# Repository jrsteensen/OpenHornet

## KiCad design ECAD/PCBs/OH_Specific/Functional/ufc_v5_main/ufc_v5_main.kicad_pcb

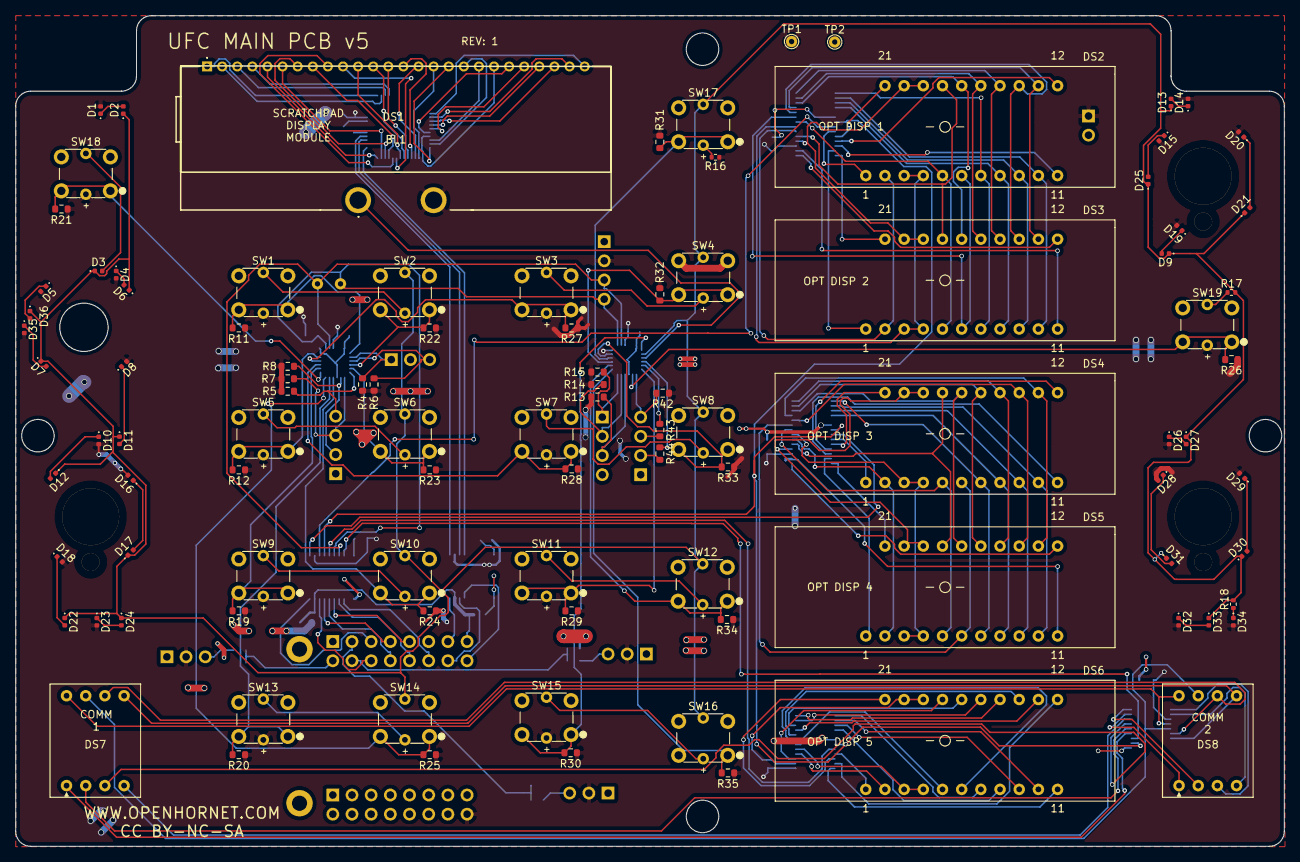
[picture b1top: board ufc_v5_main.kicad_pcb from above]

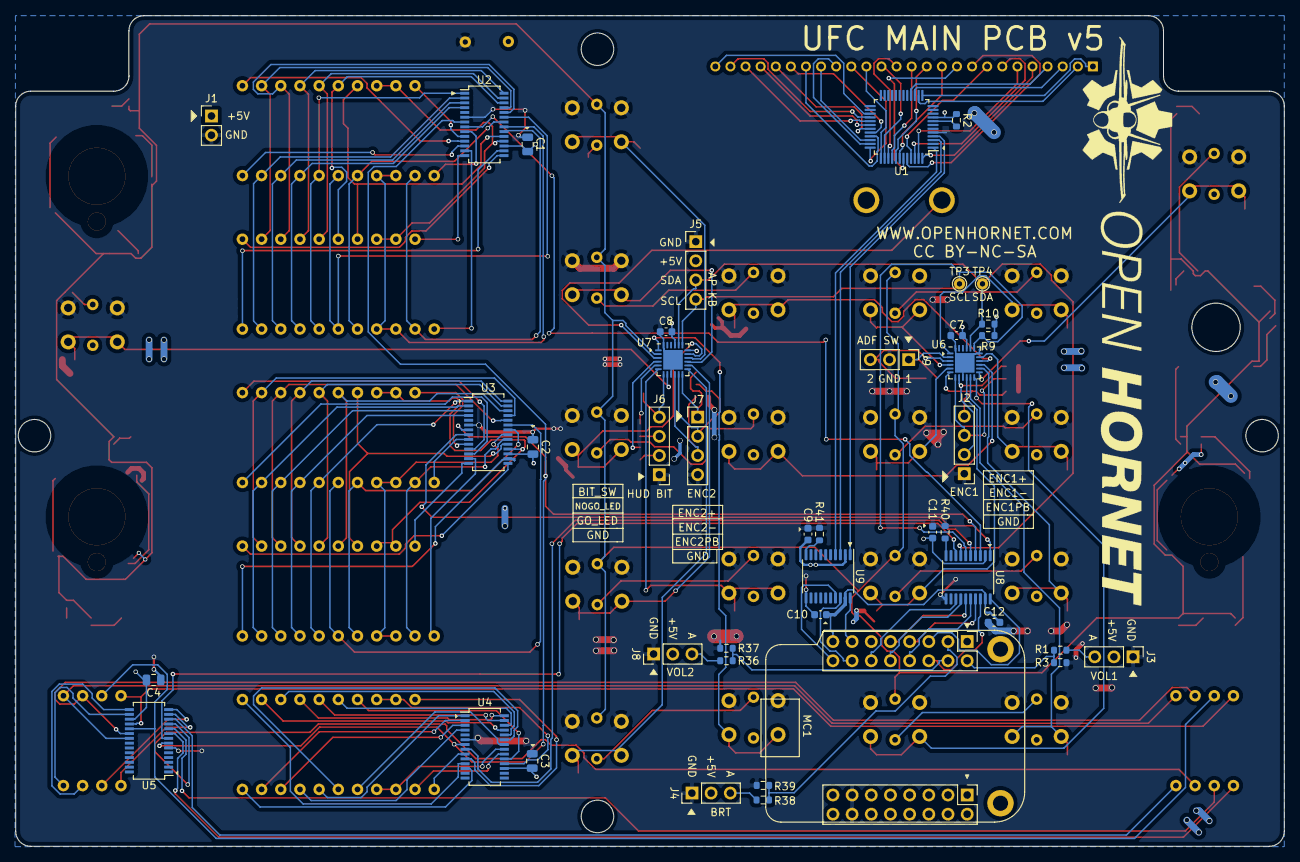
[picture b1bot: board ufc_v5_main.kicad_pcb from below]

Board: 2 copper layers, 168.0 x 110.0 mm, 149 parts (42 on the bottom side), 198 nets.

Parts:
BL1: UFCScratchPadBacklight; SCRATCHPADBACKLIGHT
C1, C2, C3, C4: 10uF; C_0805_2012Metric
C7, C8, C9, C10, C11, C12: .1uF; C_0603_1608Metric
D1, D2, D3, D4, D5, D6, D7, D8, D9, D10, D11, D12, D13, D14, D15, D16, D17, D18, D19, D20, D21, D22, D23, D24, D25, D26, D27, D28, D29, D30, D31, D32, D33, D34, D35, D36: LED_0402_1005Metric
DS1: UFCScratchpadLCD; SCRATCHPADLCD
DS2, DS3, DS4, DS5, DS6: UFCOptionDigit
DS7, DS8: UFCSingleDigit
J1: +5VIN; PinHeader_1x02_P2.54mm_Vertical
J2: ENC1; PinHeader_1x04_P2.54mm_Vertical
J3: VOL1; PinHeader_1x03_P2.54mm_Vertical
J4: BRT; PinHeader_1x03_P2.54mm_Vertical
J5: AP KB; PinHeader_1x04_P2.54mm_Vertical
J6: HUD BIT; PinHeader_1x04_P2.54mm_Vertical
J7: ENC2; PinHeader_1x04_P2.54mm_Vertical
J8: VOL2; PinHeader_1x03_P2.54mm_Vertical
J9: ADF SW; PinHeader_1x03_P2.54mm_Vertical
MC1: S2_MINI
MK1, MK2, MK3, MK4: MH; MountingHole_4.3mm_M4
MK5: SW_ADF; MountingHole_6.4mm_M6
POT1: VOL1; BR10K_Pot_11mm_x_11mm
POT2: VOL2; BR10K_Pot_11mm_x_11mm
POT3: BRT; BR10K_Pot_11mm_x_11mm
R1, R36, R38: 1k; R_0603_1608Metric
R2: 10K; R_0603_1608Metric
R3, R37, R39: 2K; R_0603_1608Metric
R4, R5, R6, R7, R8, R9, R10, R11, R12, R13, R14, R15, R19, R20, R21, R22, R23, R24, R25, R26, R27, R28, R29, R30, R31, R32, R33, R34, R35, R40, R41, R42: 4.7k; R_0603_1608Metric
R16, R17, R18: 33; R_0402_1005Metric
R43, R44: 68; R_0603_1608Metric
SW1, SW2, SW3, SW4, SW5, SW6, SW7, SW8, SW9, SW10, SW11, SW12, SW13, SW14, SW15, SW16, SW17, SW18, SW19: TL1240GQ
TP1: 5V; TestPoint_THTPad_D1.5mm_Drill0.7mm
TP2: GND; TestPoint_THTPad_D1.5mm_Drill0.7mm
TP3: SCL; TestPoint_THTPad_D1.5mm_Drill0.7mm
TP4: SDA; TestPoint_THTPad_D1.5mm_Drill0.7mm
U1: HT1621B; LQFP-48_7x7mm_P0.5mm
U2, U3, U4, U5: GN1640T; SSOP-28_3.9x9.9mm_P0.635mm
U6, U7: AW9523BTQR; WQFN-24-1EP_4x4mm_P0.5mm_EP2.6x2.6mm
U8, U9: TXS0108EPW; TSSOP-20_4.4x6.5mm_P0.65mm

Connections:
+3V3: C10.2, C12.2, MC1.8, U8.19, U9.19
+5V: BL1.2, C1.2, C2.2, C3.2, C4.2, C7.2, C8.2, C9.2, C11.2, D1.2, D4.2, D5.2, D8.2, D10.2, D14.2, D15.2, D16.2, D18.2, D19.2, D20.2, D23.2, D26.2, D28.2, D29.2, D32.2, D34.2, D35.2, J1.1, J3.2, J4.2, J5.2, J8.2, MC1.32, R2.1, R4.1, R5.2, R6.2, R7.2, R8.1, R9.1, R10.2, R11.1, R12.1, R13.1, R14.2, R15.1, R16.1, R19.1, R20.1, R21.1, R22.1, R23.1, R24.1, R25.1, R26.1, R27.1, R28.1, R29.1, R30.1, R31.1, R32.1, R33.1, R34.1, R35.1, R42.1, SW1.5, SW3.5, SW5.5, SW7.5, SW9.5, SW11.5, SW13.5, SW15.5, SW18.5, SW19.5, TP1.1, U1.9, U2.17, U3.17, U4.17, U5.17, U6.21, U7.18, U7.21, U8.2, U9.2
/0+: SW13.6, SW14.5
/0-: D2.1, D3.1, D6.1, D7.1, D9.1, D11.1, D12.1, D13.1, D17.1, D21.1, D22.1, D24.1, D25.1, D27.1, D30.1, D31.1, D33.1, D36.1, R17.2, R18.2, SW2.6, SW4.6, SW6.6, SW8.6, SW10.6, SW12.6, SW14.6, SW16.6, SW17.6, U7.2
/1-: SW1.6, SW2.5
/1AB: DS2.19, DS2.20, DS3.19, DS3.20, U2.18
/1C: DS2.18, DS3.18, U2.19
/1D: DS2.2, DS3.2, U2.20
/1DP: DS2.8, DS3.8, U2.4
/1EF: DS2.3, DS2.4, DS3.3, DS3.4, U2.21
/1G: DS2.5, DS3.5, U2.22
/1H: DS2.6, DS3.6, U2.23
/1I: DS2.13, DS3.13, U2.25
/1J: DS2.14, DS3.14, U2.24
/1K: DS2.15, DS3.15, U2.28
/1L: DS2.16, DS3.16, U2.27
/1M: DS2.17, DS3.17, U2.26
/1N: DS2.9, DS3.9, U2.3
/1O: DS2.10, DS3.10, U2.2
/1P: DS2.7, DS3.7, U2.1
/2AB: DS4.19, DS4.20, DS5.19, DS5.20, U3.18
/2C: DS4.18, DS5.18, U3.19
/2D: DS4.2, DS5.2, U3.20
/2DP: DS4.8, DS5.8, U3.4
/2EF: DS4.3, DS4.4, DS5.3, DS5.4, U3.21
/2G: DS4.5, DS5.5, U3.22
/2H: DS4.6, DS5.6, U3.23
/2I: DS4.13, DS5.13, U3.25
/2J: DS4.14, DS5.14, U3.24
/2K: DS4.15, DS5.15, U3.28
/2L: DS4.16, DS5.16, U3.27
/2M: DS4.17, DS5.17, U3.26
/2N: DS4.9, DS5.9, U3.3
/2O: DS4.10, DS5.10, U3.2
/2P: DS4.7, DS5.7, U3.1
/3-: SW3.6, SW4.5
/3AB: DS6.19, DS6.20, U4.18
/3C: DS6.18, U4.19
/3D: DS6.2, U4.20
/3DP: DS6.8, U4.4
/3EF: DS6.3, DS6.4, U4.21
/3G: DS6.5, U4.22
/3H: DS6.6, U4.23
/3I: DS6.13, U4.25
/3J: DS6.14, U4.24
/3K: DS6.15, U4.28
/3L: DS6.16, U4.27
/3M: DS6.17, U4.26
/3N: DS6.9, U4.3
/3O: DS6.10, U4.2
/3P: DS6.7, U4.1
/4-: SW5.6, SW6.5
/6-: SW7.6, SW8.5
/7-: SW9.6, SW10.5
/9-: SW11.6, SW12.5
/ADF1: J9.1, R4.2, U6.2
/ADF2: J9.3, R6.1, U6.3
/BIT_SW: J6.4, R42.2, U7.7
/CLR-: SW15.6, SW16.5
/COM0: DS1.1, U1.13
/COM1: DS1.2, U1.14
/COM2: DS1.3, U1.15
/COM3: DS1.4, U1.16
/C_GRID1: DS7.8, DS8.8, U5.18
/C_GRID2: DS7.7, DS8.7, U5.19
/C_GRID3: DS7.6, DS8.6, U5.20
/C_GRID4: DS7.5, DS8.5, U5.21
/C_SEG1: DS7.1, U5.9
/C_SEG2: DS7.2, U5.10
/C_SEG3: DS7.3, U5.11
/C_SEG4: DS7.4, U5.12
/C_SEG5: DS8.1, U5.13
/C_SEG6: DS8.2, U5.14
/C_SEG7: DS8.3, U5.15
/C_SEG8: DS8.4, U5.16
/EM-: R17.1, SW19.6
/ENC1+: J2.4, R5.1, U6.6
/ENC1-: J2.3, R7.1, U6.7
/ENC1PB: J2.2, R8.2, U6.8
/ENC2+: J7.1, R15.2, U7.12
/ENC2-: J7.2, R14.1, U7.11
/ENC2PB: J7.3, R13.2, U7.10
/GO_LED: J6.2, R44.2
/IP-: D3.2, SW18.6
/NOGO_LED: J6.3, R43.2
/OP1+: R16.2, SW17.5
/OP1D1: DS2.1, U2.9
/OP1D2: DS2.21, U2.10
/OP1D3: DS2.12, U2.11
/OP1D4: DS2.11, U2.12
/OP2D1: DS3.1, U2.13
/OP2D2: DS3.21, U2.14
/OP2D3: DS3.12, U2.15
/OP2D4: DS3.11, U2.16
/OP3D1: DS4.1, U3.9
/OP3D2: DS4.21, U3.10
/OP3D3: DS4.12, U3.11
/OP3D4: DS4.11, U3.12
/OP4D1: DS5.1, U3.13
/OP4D2: DS5.21, U3.14
/OP4D3: DS5.12, U3.15
/OP4D4: DS5.11, U3.16
/OP5D1: DS6.1, U4.9
/OP5D2: DS6.21, U4.10
/OP5D3: DS6.12, U4.11
/OP5D4: DS6.11, U4.12
/SEG0: DS1.5, U1.48
/SEG1: DS1.6, U1.47
/SEG2: DS1.7, U1.46
/SEG3: DS1.8, U1.45
/SEG4: DS1.9, U1.44
/SEG5: DS1.10, U1.43
/SEG6: DS1.11, U1.42
/SEG7: DS1.12, U1.41
/SEG8: DS1.13, U1.40
/SEG9: DS1.14, U1.39
/SEG10: DS1.15, U1.38
/SEG11: DS1.16, U1.37
/SEG12: DS1.17, U1.36
/SEG13: DS1.18, U1.35
/SEG14: DS1.19, U1.34
/SEG15: DS1.20, U1.33
/SEG16: DS1.21, U1.32
/SEG17: DS1.22, U1.31
/SEG18: DS1.23, U1.30
/SEG19: DS1.24, U1.29
/SEG20: DS1.25, U1.28
/SEG21: DS1.26, U1.27
/SW1: R11.2, SW1.1, U6.1
/SW2: R22.2, SW2.1, U6.4
/SW3: R27.2, SW3.1, U6.16
/SW4: R12.2, SW5.1, U6.17
/SW5: R23.2, SW6.1, U6.5
/SW6: R28.2, SW7.1, U6.15
/SW7: R19.2, SW9.1, U6.14
/SW8: R24.2, SW10.1, U6.10
/SW9: R29.2, SW11.1, U7.6
/SW10: R30.2, SW15.1, U7.1
/SW11: R20.2, SW13.1, U6.11
/SW12: R25.2, SW14.1, U6.12
/SW13: R21.2, SW18.1, U6.13
/SW14: R31.2, SW17.1, U7.16
/SW15: R32.2, SW4.1, U7.15
/SW16: R33.2, SW8.1, U7.17
/SW17: R34.2, SW12.1, U7.14
/SW18: R35.2, SW16.1, U7.13
/SW19: R26.2, SW19.1, U7.8
/TNLEDPWR: BL1.1, U7.3
ANALOG1: J3.3, R1.1
ANALOG1@3.3V: MC1.9, R1.2, R3.1
ANALOG2: J8.3, R36.1
ANALOG2@3.3V: MC1.10, R36.2, R37.1
ANALOG3: J4.3, R38.1
ANALOG3@3.3V: MC1.2, R38.2, R39.1
C_CLK: U5.8, U8.8
C_CLK@3.3V: MC1.14, U8.13
DIO: U2.7, U3.7, U4.7, U5.7, U8.4
DIO@3.3V: MC1.4, U8.17
GND: C1.1, C2.1, C3.1, C4.1, C7.1, C8.1, C9.1, C10.1, C11.1, C12.1, J1.2, J2.1, J3.1, J4.1, J5.1, J6.1, J7.4, J8.1, J9.2, MC1.23, MC1.31, R3.2, R37.2, R39.2, R40.2, R41.2, SW1.2, SW2.2, SW3.2, SW4.2, SW5.2, SW6.2, SW7.2, SW8.2, SW9.2, SW10.2, SW11.2, SW12.2, SW13.2, SW14.2, SW15.2, SW16.2, SW17.2, SW18.2, SW19.2, TP2.1, U1.5, U2.6, U3.6, U4.6, U5.6, U6.9, U6.18, U6.24, U6.25, U7.9, U7.24, U7.25, U8.11, U9.11
unnamed: D1.1, D2.2
unnamed: D4.1, D6.2
unnamed: D10.1, D12.2
unnamed: D8.1, D11.2
unnamed: D13.2, D14.1
unnamed: D15.1, D25.2
unnamed: D16.1, D17.2
unnamed: D18.1, D22.2
unnamed: D9.2, D19.1
unnamed: D20.1, D21.2
unnamed: D23.1, D24.2
unnamed: D26.1, D27.2
unnamed: D28.1, D31.2
unnamed: D29.1, D30.2
unnamed: D32.1, D33.2
unnamed: D34.1, R18.1
unnamed: D7.2, D35.1
unnamed: D5.1, D36.2
unnamed: R2.2, U1.8
unnamed: R40.1, U8.10
unnamed: R41.1, U9.10
unnamed: R43.1, U7.5
unnamed: R44.1, U7.4
OP1_CLK: U2.8, U8.3
OP1_CLK@3.3V: MC1.11, U8.18
OP2_CLK: U3.8, U8.1
OP2_CLK@3.3V: MC1.3, U8.20
OP3_CLK: U4.8, U8.5
OP3_CLK@3.3V: MC1.12, U8.16
SCL: J5.4, R9.2, TP3.1, U6.19, U7.19, U8.6
SCL@3.3V: MC1.5, U8.15
SCRCS: U1.1, U9.4
SCRCS@3.3V: MC1.16, U9.17
SCRDATA: U1.4, U9.1
SCRDATA@3.3V: MC1.7, U9.20
SCRWR: U1.3, U9.3
SCRWR@3.3V: MC1.15, U9.18
SDA: J5.3, R10.1, TP4.1, U6.20, U7.20, U8.7
SDA@3.3V: MC1.13, U8.14

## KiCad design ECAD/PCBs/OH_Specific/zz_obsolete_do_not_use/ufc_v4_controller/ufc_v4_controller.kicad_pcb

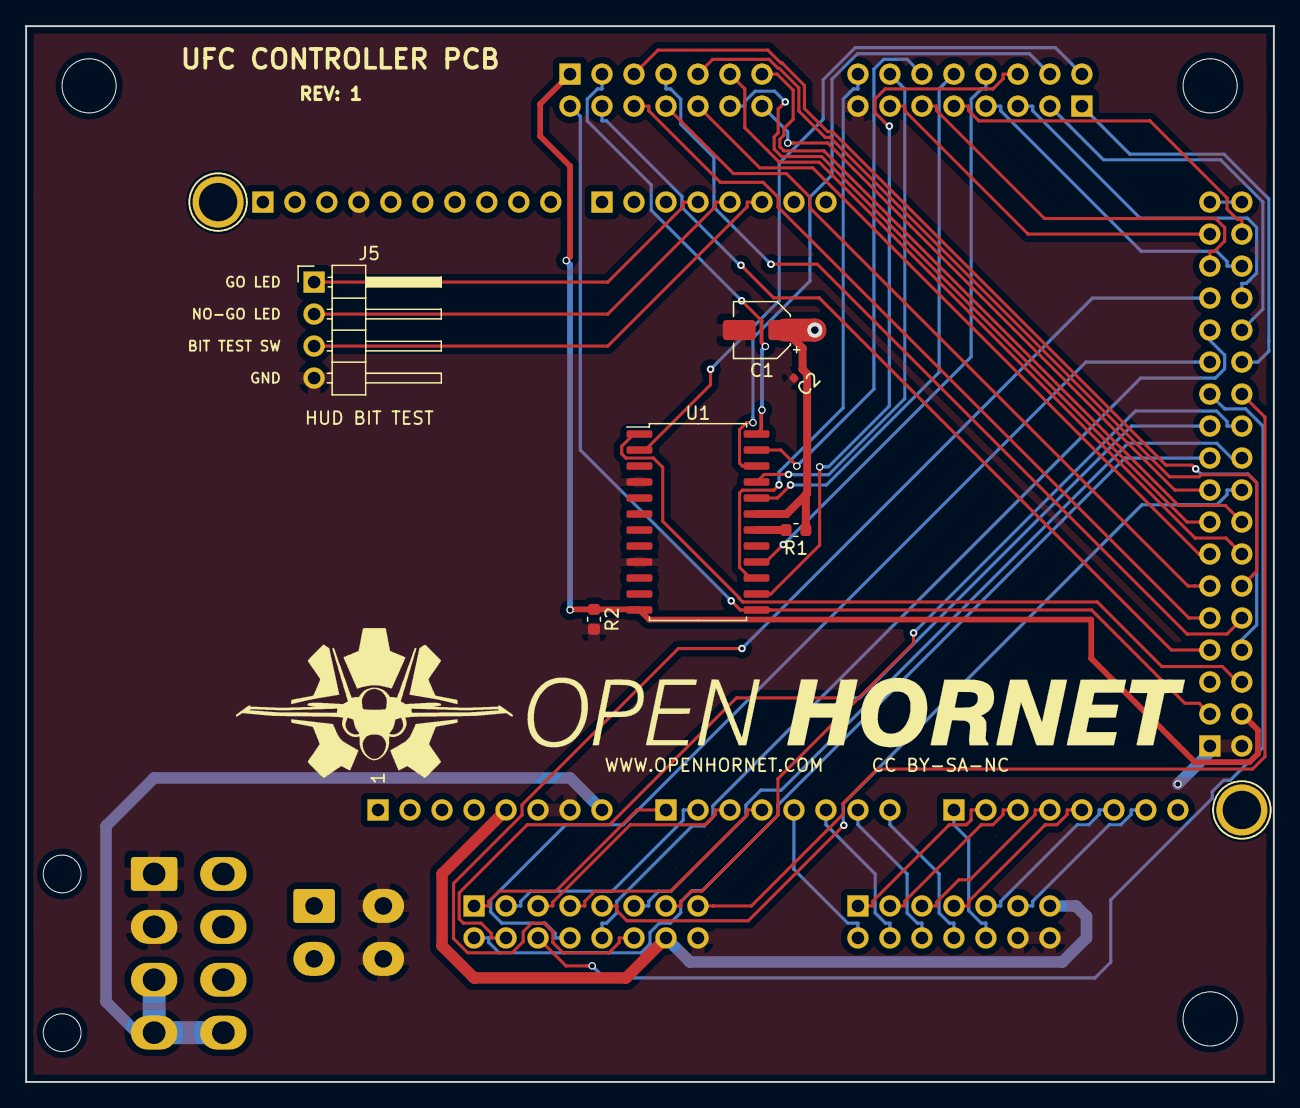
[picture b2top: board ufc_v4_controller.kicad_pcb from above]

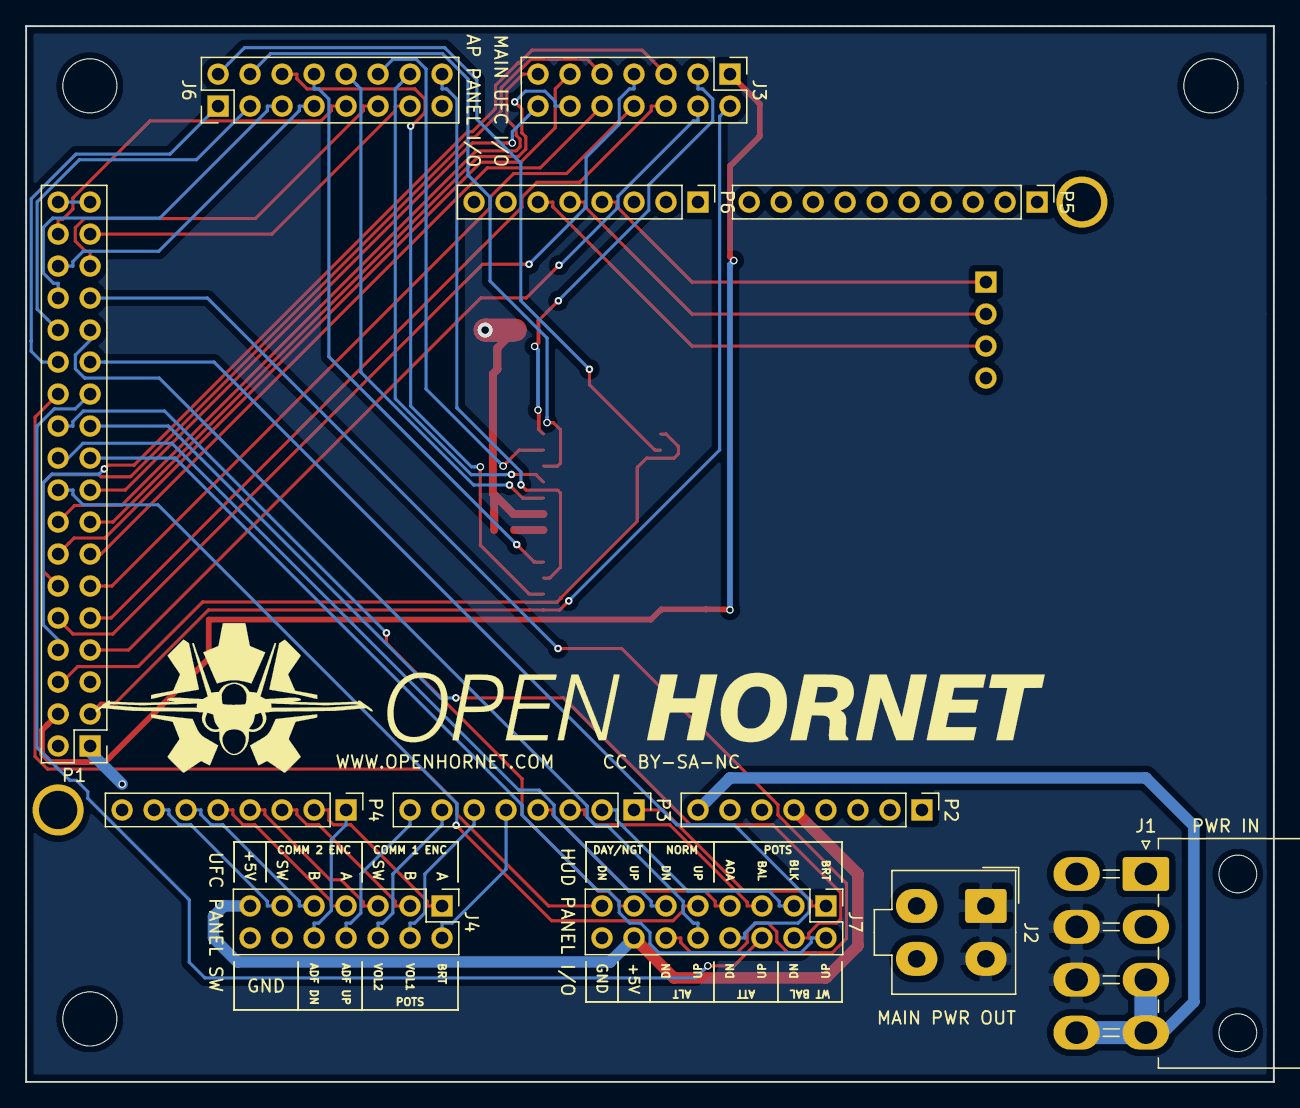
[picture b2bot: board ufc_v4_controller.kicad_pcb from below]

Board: 2 copper layers, 99.1 x 83.8 mm, 23 parts (12 on the bottom side), 64 nets.

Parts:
C1: 10uF; CP_Elec_4x5.3
C2: 100nF; C_0402_1005Metric
H1, H2, H3: MountingHole_4.3mm_M4
J1: PWR IN; Molex_Mini-Fit_Jr_5569-08A2_2x04_P4.20mm_Horizontal
J2: MAIN PWR OUT; Molex_Mini-Fit_Jr_5566-04A_2x02_P4.20mm_Vertical
J3: MAIN UFC I/O; PinHeader_2x07_P2.54mm_Vertical
J4: UFC PANEL SW; PinHeader_2x07_P2.54mm_Vertical
J5: HUD BIT TEST; PinHeader_1x04_P2.54mm_Horizontal
J6: AP PANEL I/O; PinHeader_2x08_P2.54mm_Vertical
J7: HUD PANEL I/O; PinHeader_2x08_P2.54mm_Vertical
MK3, MK4: MH; Arduino_1pin
P1: Digital; PinHeader_2x18_P2.54mm_Vertical
P2: Power; PinHeader_1x08_P2.54mm_Vertical
P3, P4: Analog; PinHeader_1x08_P2.54mm_Vertical
P5: PWM; PinHeader_1x10_P2.54mm_Vertical
P6: PWM; PinHeader_1x08_P2.54mm_Vertical
R1: 25.5K; R_0603_1608Metric
R2: 10K; R_0603_1608Metric
U1: MAX7219EWG+T; SOIC-24W_7.5x15.4mm_P1.27mm

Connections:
+5V: J4.13, J7.14, P2.5
+5VD: P1.35, P1.36
/2(**): J5.3, P6.6
/3(**): J5.2, P6.5
/4(**): J5.1, P6.4
/22: J6.13, P1.33
/23: J6.9, P1.34
/24: J6.11, P1.31
/25: J6.7, P1.32
/26: J7.12, P1.29
/27: J6.5, P1.30
/28: J7.10, P1.27
/29: J6.3, P1.28
/30: J7.8, P1.25
/31: J6.1, P1.26
/32: J7.6, P1.23
/33: J7.15, P1.24
/34: J7.4, P1.21
/35: J7.13, P1.22
/36: J7.2, P1.19
/37: J7.11, P1.20
/38: J3.14, P1.17
/39: J7.9, P1.18
/40: J3.12, P1.15
/41: J3.13, P1.16
/42: J3.10, P1.13
/43: J3.11, P1.14
/44: J3.8, P1.11
/45: J3.9, P1.12
/46: J3.6, P1.9
/47: J3.7, P1.10
/48: J3.4, P1.7
/49: J3.5, P1.8
/51(MOSI): P1.6, U1.1
/52(SCK): J3.2, P1.3, U1.13
/53(SS): J3.1, P1.4, R2.1, U1.12
/+5V_SUPPLY: C1.1, C2.1, J1.6, J1.7, J2.1, J2.2, R1.1, U1.19
/+12V_SUPPLY: J1.3, J1.4, J1.8, P2.8
/A0: J7.1, P3.1
/A1: J7.3, P3.2
/A2: J7.5, P3.3
/A3: J7.7, P3.4
/A4: J4.2, P3.5
/A5: J4.4, P3.6
/A6: J4.6, P3.7
/A7: J4.8, P3.8
/A8: J4.10, P4.1
/A9: J4.1, P4.2
/A10: J4.3, P4.3
/A11: J4.5, P4.4
/A12: J4.7, P4.5
/A13: J4.9, P4.6
/A14: J4.11, P4.7
/DIG0: J6.2, U1.2
/DIN2: J3.3, U1.24
/SEGA: J6.6, U1.14
/SEGB: J6.8, U1.16
/SEGC: J6.10, U1.20
/SEGD: J6.12, U1.23
/SEGDP: J6.4, U1.22
/SEGE: J6.14, U1.21
/SEGF: J6.16, U1.15
GND: C1.2, C2.2, J1.1, J1.2, J2.3, J2.4, J4.12, J4.14, J5.4, J6.15, J7.16, P1.1, P1.2, P2.6, P2.7, P5.4, R2.2, U1.4, U1.9
unnamed: R1.2, U1.18

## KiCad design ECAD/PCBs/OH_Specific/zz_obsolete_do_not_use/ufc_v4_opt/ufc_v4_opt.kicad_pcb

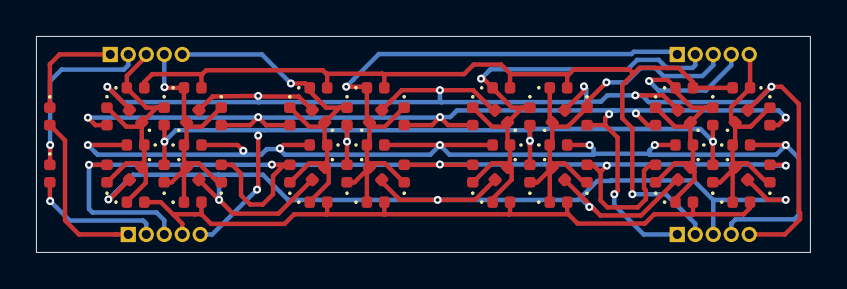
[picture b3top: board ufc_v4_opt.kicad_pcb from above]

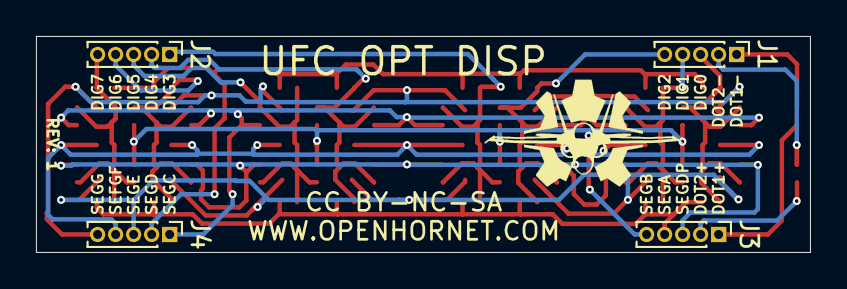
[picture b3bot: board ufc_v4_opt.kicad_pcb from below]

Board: 2 copper layers, 43.0 x 12.0 mm, 70 parts (4 on the bottom side), 20 nets.

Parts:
D1, D2, D3, D4, D5, D6, D7, D8, D9, D10, D11, D12, D13, D14, D15, D16, D17, D18, D19, D20, D21, D22, D23, D24, D25, D26, D27, D28, D29, D30, D31, D32, D33, D34, D35, D36, D37, D38, D39, D40, D41, D42, D43, D44, D45, D46, D47, D48, D49, D50, D51, D52, D53, D54, D55, D56, D57, D58, D59, D60, D61, D62, D63, D64, D65, D66: LED; LED_0402_1005Metric
J1, J2, J3, J4: Conn_01x05_Male; PinHeader_1x05_P1.00mm_Vertical

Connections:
/DIG0: D1.1, D2.1, D3.1, D4.1, D5.1, D6.1, D7.1, D8.1, J1.3
/DIG1: D9.1, D10.1, D11.1, D12.1, D13.1, D14.1, D15.1, D16.1, J1.4
/DIG2: D17.1, D18.1, D19.1, D20.1, D21.1, D22.1, D23.1, D24.1, J1.5
/DIG3: D25.1, D26.1, D27.1, D28.1, D29.1, D30.1, D31.1, D32.1, J2.1
/DIG4: D33.1, D34.1, D35.1, D36.1, D37.1, D38.1, D39.1, D40.1, J2.2
/DIG5: D41.1, D42.1, D43.1, D44.1, D45.1, D46.1, D47.1, D48.1, J2.3
/DIG6: D49.1, D50.1, D51.1, D52.1, D53.1, D54.1, D55.1, D56.1, J2.4
/DIG7: D57.1, D58.1, D59.1, D60.1, D61.1, D62.1, D63.1, D64.1, J2.5
/DOT1+: D65.2, J3.1
/DOT1-: D65.1, J1.1
/DOT2+: D66.2, J3.2
/DOT2-: D66.1, J1.2
/SEGA: D7.2, D14.2, D23.2, D30.2, D39.2, D46.2, D55.2, D62.2, J3.4
/SEGB: D8.2, D9.2, D24.2, D25.2, D40.2, D41.2, D56.2, D57.2, J3.5
/SEGC: D1.2, D15.2, D17.2, D31.2, D33.2, D47.2, D49.2, D63.2, J4.1
/SEGD: D3.2, D10.2, D19.2, D26.2, D35.2, D42.2, D51.2, D58.2, J4.2
/SEGDP: D2.2, D16.2, D18.2, D32.2, D34.2, D48.2, D50.2, D64.2, J3.3
/SEGE: D6.2, D13.2, D22.2, D29.2, D38.2, D45.2, D54.2, D61.2, J4.3
/SEGF: D5.2, D12.2, D21.2, D28.2, D37.2, D44.2, D53.2, D60.2, J4.4
/SEGG: D4.2, D11.2, D20.2, D27.2, D36.2, D43.2, D52.2, D59.2, J4.5

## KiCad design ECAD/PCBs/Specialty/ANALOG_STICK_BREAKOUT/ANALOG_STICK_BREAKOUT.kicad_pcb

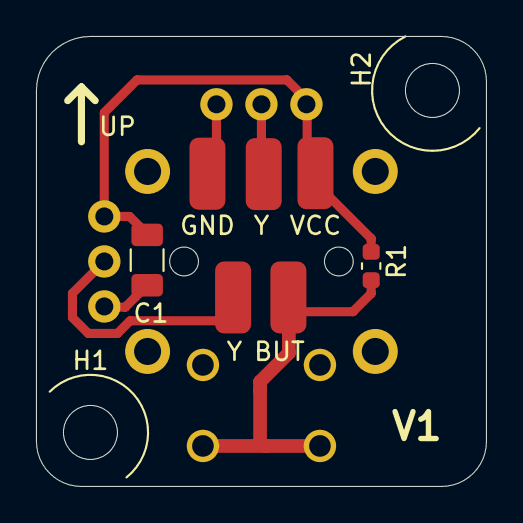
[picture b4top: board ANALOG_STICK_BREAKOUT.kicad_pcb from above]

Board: 2 copper layers, 25.0 x 25.0 mm, 10 parts (1 on the bottom side), 5 nets.

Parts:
C1: 4.7uF; C_1206_3216Metric
H1, H2: MountingHole; MountingHole_3mm
J2, J3, J4, J5, J6: Conn_01x01; SolderWirePad_1x01_SMD_2x4mm
JOY1: ANALOGSTICK_CENTERPUSH; RKJXV12
R1: 10k; R_0603_1608Metric

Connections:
GND: C1.2, J6.1, JOY1.1, JOY1.4, JOY1.a, JOY1.c
unnamed: J3.1, JOY1.5
unnamed: J4.1, JOY1.2
unnamed: J5.1, JOY1.b, JOY1.d, R1.2
VCC: C1.1, J2.1, JOY1.3, JOY1.6, R1.1

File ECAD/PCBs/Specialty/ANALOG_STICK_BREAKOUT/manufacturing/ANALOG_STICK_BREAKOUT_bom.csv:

Comment,Designator,Footprint,LCSC
"4.7uF","C1","Capacitor_SMD:C_1206_3216Metric","C29823"
"MountingHole","H1,H2","MountingHole:MountingHole_3mm",""
"Conn_01x01","J2,J3,J4,J5,J6","KiCAD_Libraries:SolderWirePad_1x01_SMD_2x4mm",""
"ANALOGSTICK_CENTERPUSH","JOY1","KiCAD_Libraries:RKJXV12",""
"10k","R1","Resistor_SMD:R_0603_1608Metric",""

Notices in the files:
ECAD/PCBs/OH_Specific/Functional/ufc_v5_main/ufc_v5_main.kicad_pcb:
CC BY-NC-SA
ECAD/PCBs/OH_Specific/zz_obsolete_do_not_use/ufc_v4_controller/ufc_v4_controller.kicad_pcb:
WWW.OPENHORNET.COM CC BY-SA-NC
